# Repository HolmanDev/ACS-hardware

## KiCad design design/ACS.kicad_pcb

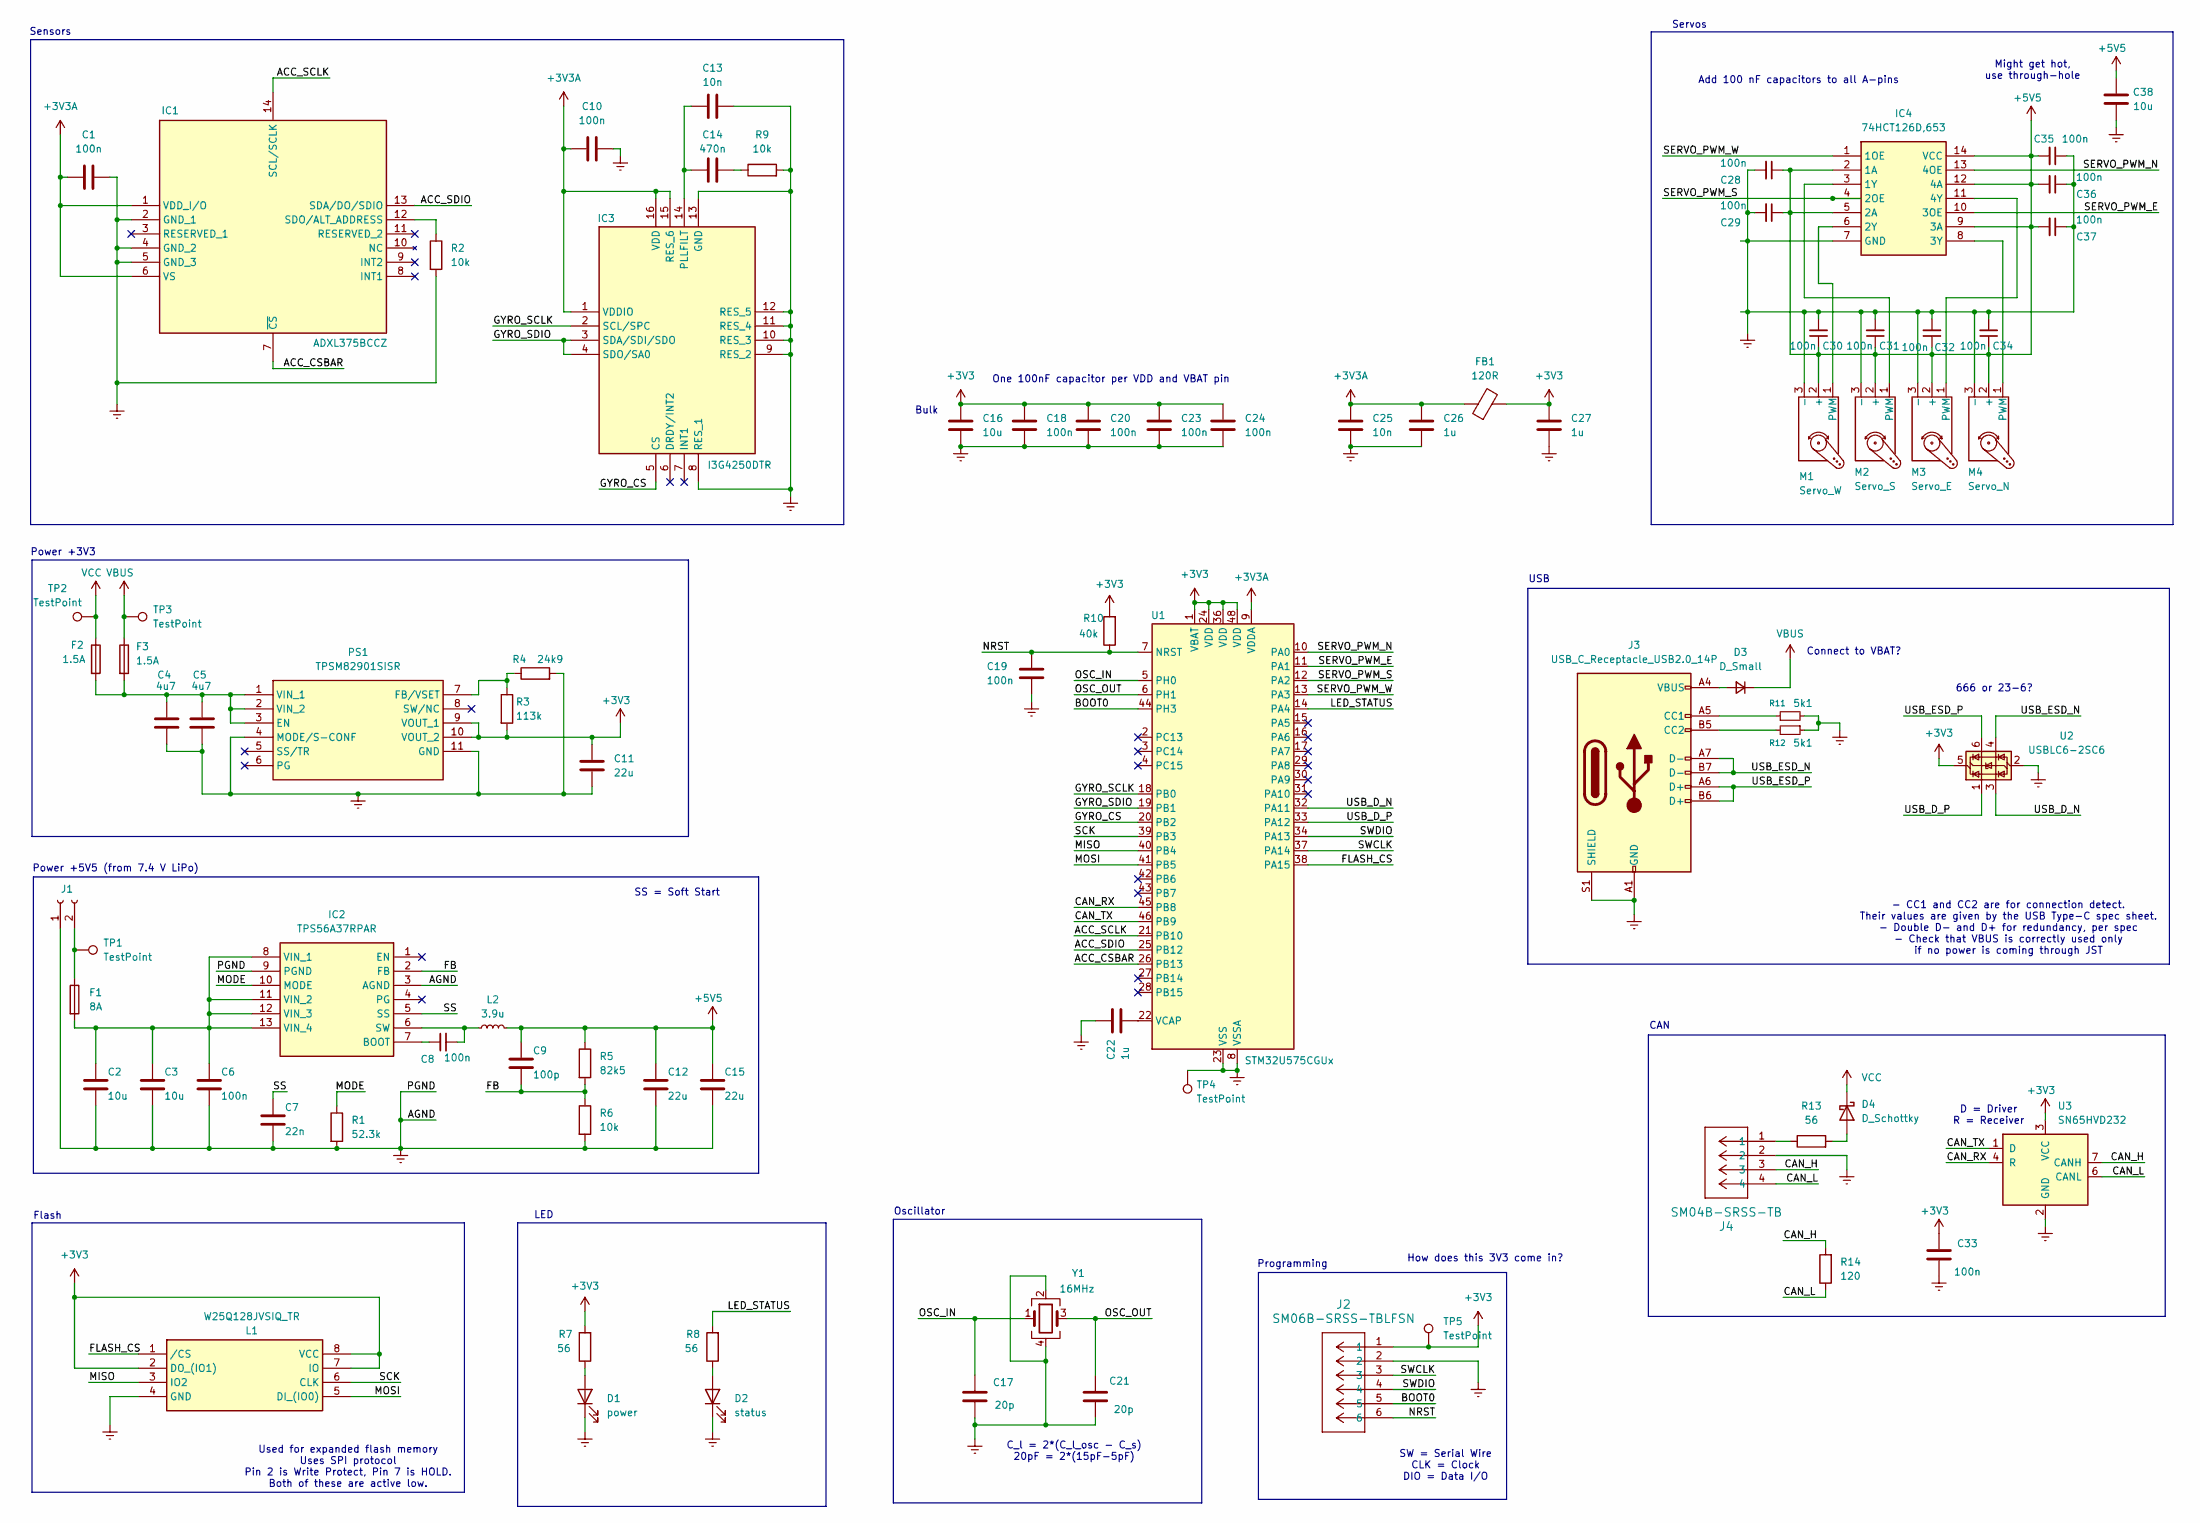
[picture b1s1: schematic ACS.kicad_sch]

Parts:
C1, C6, C8, C10, C18, C19, C20, C23, C24, C28, C29, C30, C31, C32, C33, C34, C35, C36, C37: 100n; CAPC0603X35N
C2, C3, C16: 10u; CAPC2012X135N
C4, C5: 4u7; CAPC0603X55N
C7: 22n; CAPC1005X55N
C9: 100p; CAPC0603X33N
C11, C12, C15: 22u; GRM18x
C13, C25: 10n; CAPC1005X55N
C14: 470n; GRM033D70J224ME01D
C17, C21: 20p; GRM033D70J224ME01D
C22, C26, C27: 1u; GRT155R71H472KE01D
C38: 10u; CAPAE530X550N
D1: power; LEDC1608X85N
D2: status; LEDC1608X85N
D3: D_Small; NSR0530HT3G
D4: D_Schottky; NSR0530HT3G
F1: 8A; FUSC6125X279N
F2, F3: 1.5A; FUSC6125X279N
FB1: 120R; RESC3216X60N
IC1: ADXL375BCCZ; CC-14-1; Mouser Part Number 584-ADXL375BCCZ
IC2: TPS56A37RPAR; Mouser Part Number 595-TPS56A37RPAR
IC3: I3G4250DTR; LGA-16L_4X4X1.1MM_; Mouser Part Number 511-I3G4250DTR
IC4: 74HCT126D,653; SOIC127P600X175-14N; Mouser Part Number 771-74HCT126D-T
J1: XT30
J2: SM06B-SRSS-TBLFSN; CONN_SM06B-SRSS-TB_JST
J3: USB_C_Receptacle_USB2.0_14P; USB_C_Receptacle_Palconn_UTC16-G fixed
J4: SM04B-SRSS-TB; CONN_SM04B-SRSS-TB_JST
L1: W25Q128JVSIQ_TR; SOIC127P780X195-8N; Mouser Part Number 454-W25Q128JVSIQTR
L2: 3.9u; INDPM110100X400N
M1: Servo_W; PinHeader_1x03_P2.54mm_Vertical
M2: Servo_S; PinHeader_1x03_P2.54mm_Vertical
M3: Servo_E; PinHeader_1x03_P2.54mm_Vertical
M4: Servo_N; PinHeader_1x03_P2.54mm_Vertical
PS1: TPSM82901SISR; Mouser Part Number 595-TPSM82901SISR
R1: 52.3k; ERA3AEB101V
R2, R6, R9: 10k; RESC1608X55N
R3: 113k; ERA3AEB101V
R4: 24k9; RESC1608X55N
R5: 82k5; ERJP06D1000V
R7, R8, R13: 56; ERA2V__0402_
R10: 40k; RESC2012X50N
R11, R12: 5k1; RESC1608X55N
R14: 120; RESC3216X60N
TP1, TP2, TP3, TP4, TP5: TestPoint; TestPoint_Pad_D2.0mm
U1: STM32U575CGUx; QFN-48-1EP_7x7mm_P0.5mm_EP5.6x5.6mm
U2: USBLC6-2SC6; SOT-23-6
U3: SN65HVD232; SOIC-8_3.9x4.9mm_P1.27mm
Y1: 16MHz; SG210STF160000ML5

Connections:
+3V3: C11.1, C16.1, C18.1, C20.1, C23.1, C24.1, C27.1, C33.1, FB1.2, J2.1, L1.2 (DO_(IO1)), L1.7 (IO), L1.8 (VCC), PS1.9 (VOUT_1), PS1.10 (VOUT_2), R3.2, R7.2, R10.2, TP5.1, U1.1 (VBAT), U1.24 (VDD), U1.36 (VDD), U1.48 (VDD), U2.5 (VBUS), U3.3 (VCC)
+3V3A: C1.1, C10.1, C25.1, C26.1, FB1.1, IC1.1 (VDD_I/O), IC1.6 (VS), IC3.1 (VDDIO), IC3.15 (RES_6), IC3.16 (VDD), U1.9 (VDDA)
+5V5: C9.2, C12.2, C15.2, C28.1, C29.1, C30.1, C31.1, C32.1, C34.1, C35.2, C36.2, C37.2, C38.2, IC4.2 (1A), IC4.5 (2A), IC4.9 (3A), IC4.12 (4A), IC4.14 (VCC), L2.2, M1.2 (+), M2.2 (+), M3.2 (+), M4.2 (+), R5.1
/ACC_CSBAR: IC1.7 (~CS), U1.26 (PB13)
/ACC_SCLK: IC1.14 (SCL/SCLK), U1.21 (PB10)
/ACC_SDIO: IC1.13 (SDA/DO/SDIO), U1.25 (PB12)
/BOOT0: J2.5, U1.44 (PH3)
/CAN_H: J4.3, R14.2, U3.7 (CANH)
/CAN_L: J4.4, R14.1, U3.6 (CANL)
/CAN_RX: U1.45 (PB8), U3.4 (R)
/CAN_TX: U1.46 (PB9), U3.1 (D)
/FB: C9.1, IC2.2 (FB), R5.2, R6.1
/FLASH_CS: L1.1 (/CS), U1.38 (PA15)
/GYRO_CS: IC3.5 (CS), U1.20 (PB2)
/GYRO_SCLK: IC3.2 (SCL/SPC), U1.18 (PB0)
/GYRO_SDIO: IC3.3 (SDA/SDI/SDO), IC3.4 (SDO/SA0), U1.19 (PB1)
/LED_STATUS: R8.2, U1.14 (PA4)
/MISO: L1.3 (IO2), U1.40 (PB4)
/MODE: IC2.10 (MODE), R1.1
/MOSI: L1.5 (DI_(IO0)), U1.41 (PB5)
/NRST: C19.1, J2.6, R10.1, U1.7 (NRST)
/OSC_IN: C17.2, U1.5 (PH0), Y1.1
/OSC_OUT: C21.2, U1.6 (PH1), Y1.3
/SCK: L1.6 (CLK), U1.39 (PB3)
/SERVO_PWM_E: IC4.10 (3OE), U1.11 (PA1)
/SERVO_PWM_N: IC4.13 (4OE), U1.10 (PA0)
/SERVO_PWM_S: IC4.4 (2OE), U1.12 (PA2)
/SERVO_PWM_W: IC4.1 (1OE), U1.13 (PA3)
/SS: C7.2, IC2.5 (SS)
/SWCLK: J2.3, U1.37 (PA14)
/SWDIO: J2.4, U1.34 (PA13)
/USB_D_N: U1.32 (PA11), U2.3 (I/O2)
/USB_D_P: U1.33 (PA12), U2.1 (I/O1)
/USB_ESD_N: J3.A7 (D-), J3.B7 (D-), U2.4 (I/O2)
/USB_ESD_P: J3.A6 (D+), J3.B6 (D+), U2.6 (I/O1)
Earth: C1.2, C2.1, C3.1, C4.1, C5.1, C6.1, C7.1, C10.2, C11.2, C12.1, C13.2, C15.1, C16.2, C17.1, C18.2, C19.2, C20.2, C21.1, C22.1, C23.2, C24.2, C25.2, C26.2, C27.2, C28.2, C29.2, C30.2, C31.2, C32.2, C33.2, C34.2, C35.1, C36.1, C37.1, C38.1, D1.1 (K), D2.1 (K), IC1.2 (GND_1), IC1.4 (GND_2), IC1.5 (GND_3), IC2.3 (AGND), IC2.9 (PGND), IC3.8 (RES_1), IC3.9 (RES_2), IC3.10 (RES_3), IC3.11 (RES_4), IC3.12 (RES_5), IC3.13 (GND), IC4.7 (GND), J1.1, J2.2, J3.A1 (GND), J3.A12 (GND), J3.B1 (GND), J3.B12 (GND), J3.S1 (SHIELD), J4.2, L1.4 (GND), M1.3 (-), M2.3 (-), M3.3 (-), M4.3 (-), PS1.4 (MODE/S-CONF), PS1.11 (GND), R1.2, R2.2, R4.2, R6.2, R9.2, R11.2, R12.1, TP4.1, U1.8 (VSSA), U1.23 (VSS), U1.35 (VSS), U1.47 (VSS), U1.49 (VSS), U2.2 (GND), U3.2 (GND), Y1.2, Y1.4
unnamed: C14.2, R9.1
unnamed: D1.2 (A), R7.1
unnamed: D2.2 (A), R8.1
unnamed: D3.2 (A), J3.A4 (VBUS), J3.A9 (VBUS), J3.B4 (VBUS), J3.B9 (VBUS)
unnamed: D4.2 (A), R13.2
unnamed: IC1.12 (SDO/ALT_ADDRESS), R2.1
unnamed: C8.1, IC2.7 (BOOT)
unnamed: C8.2, IC2.6 (SW), L2.1
unnamed: C2.2, C3.2, C6.2, F1.2, IC2.8 (VIN_1), IC2.11 (VIN_2), IC2.12 (VIN_3), IC2.13 (VIN_4)
unnamed: C13.1, C14.1, IC3.14 (PLLFILT)
unnamed: IC4.3 (1Y), M2.1 (PWM)
unnamed: IC4.6 (2Y), M1.1 (PWM)
unnamed: IC4.8 (3Y), M4.1 (PWM)
unnamed: IC4.11 (4Y), M3.1 (PWM)
unnamed: F1.1, J1.2, TP1.1
unnamed: J3.A5 (CC1), R11.1
unnamed: J3.B5 (CC2), R12.2
unnamed: J4.1, R13.1
unnamed: C4.2, C5.2, F2.2, F3.2, PS1.1 (VIN_1), PS1.2 (VIN_2), PS1.3 (EN)
unnamed: PS1.7 (FB/VSET), R3.1, R4.1
unnamed: C22.2, U1.22 (VCAP)
VBUS: D3.1 (K), F3.1, TP3.1
VCC: D4.1 (K), F2.1, TP2.1

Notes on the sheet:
Add 100 nF capacitors to all A-pins
SS = Soft Start
Power +5V5 (from 7.4 V LiPo)
Bulk
C_l = 2*(C_l_osc - C_s) 20pF = 2*(15pF-5pF)
Connect to VBAT?
Might get hot, use through-hole
- CC1 and CC2 are for connection detect. Their values are given by the USB Type-C spec sheet. - Double D- and D+ for redundancy, per spec - Check that VBUS is correctly used only if no power is coming through JST
Used for expanded flash memory Uses SPI protocol Pin 2 is Write Protect, Pin 7 is HOLD. Both of these are active low.
666 or 23-6?
How does this 3V3 come in?
Flash
Programming
Power +3V3
D = Driver R = Receiver
CAN
Sensors
SW = Serial Wire CLK = Clock DIO = Data I/O
USB
Oscillator
LED
One 100nF capacitor per VDD and VBAT pin
Servos

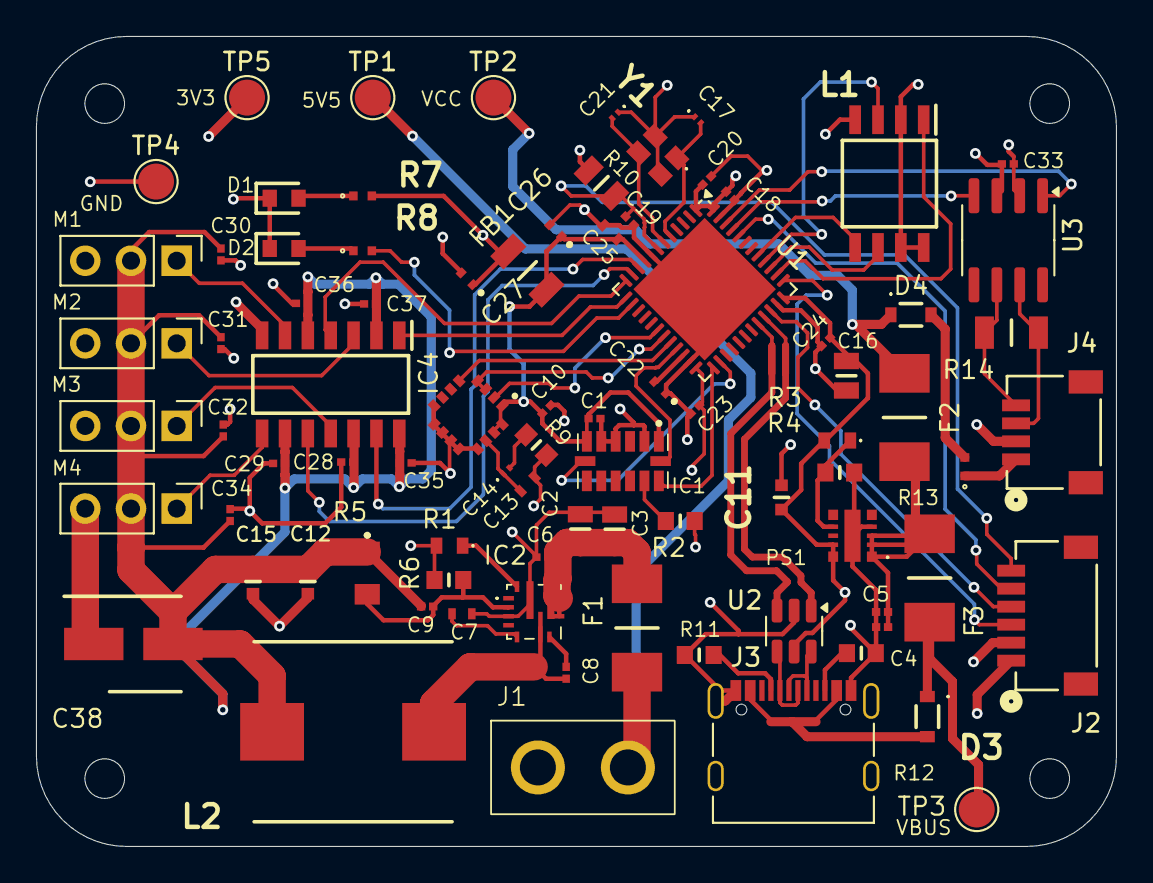
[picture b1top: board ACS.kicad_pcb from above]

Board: 4 copper layers, 60.0 x 45.0 mm, 84 parts (0 on the bottom side), 59 nets.

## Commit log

2025-10-28 fix footprint assignment and add BOM
2025-10-28 add gnd test
2025-10-29 move servo 5V5 and GND to F
2025-10-29 design review fixes
